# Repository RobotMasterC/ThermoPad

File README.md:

# ThermoPad

*Image drawn by Ever*

*https://www.youtube.com/@Ever_Draws*

A Thermometer that uses a SHT30-DIS-B2.5KS, a 0.96" OLED screen, and is controlled with a Xiao RP2040

## PCB

   - Front

   - Back

   - Schematic

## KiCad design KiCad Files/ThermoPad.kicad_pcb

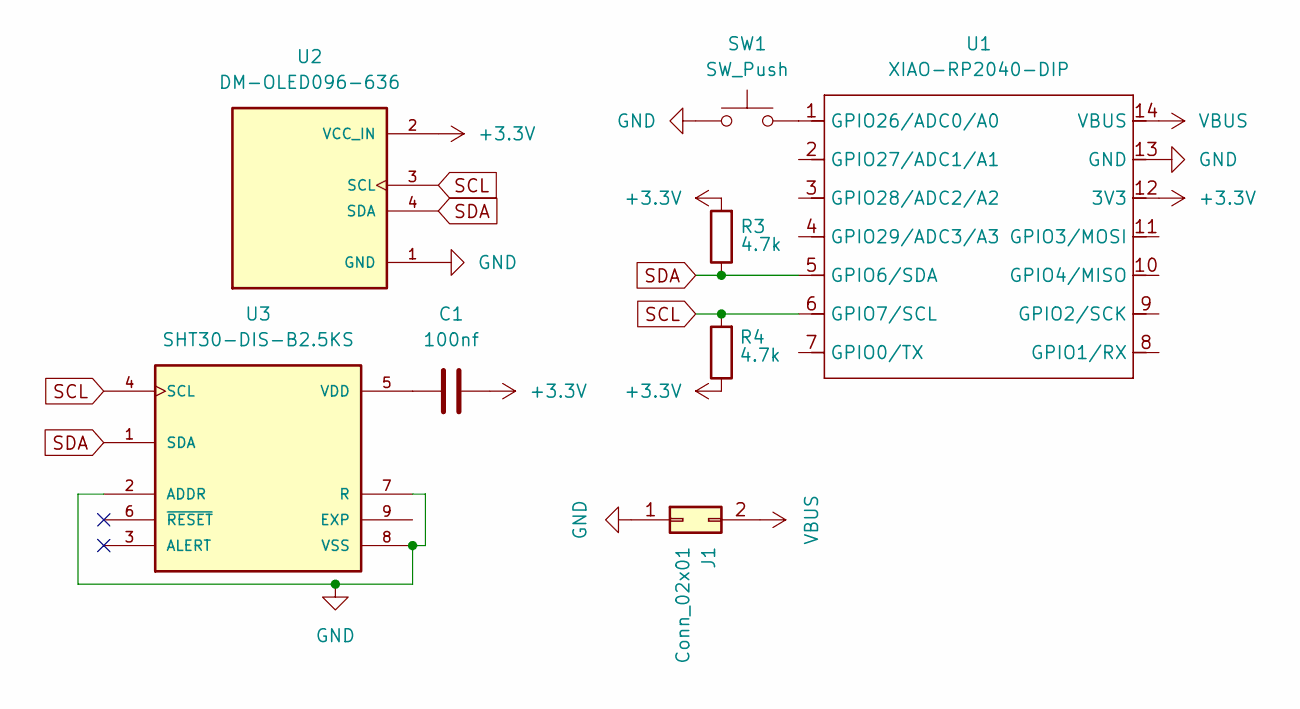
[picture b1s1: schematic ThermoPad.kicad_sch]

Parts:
C1: 100nf; C_0402_1005Metric
J1: Conn_02x01; PinHeader_1x02_P2.54mm_Horizontal
R3, R4: 4.7k; R_0402_1005Metric
SW1: SW_Push; SW_PUSH_6mm_H4.3mm
U1: XIAO-RP2040-DIP
U2: DM-OLED096-636; MODULE_DM-OLED096-636; PARTREV 2018-09-10
U3: SHT30-DIS-B2.5KS; XDCR_SHT30-DIS-B2.5KS

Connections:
+3.3V: C1.2, R3.2, R4.1, U1.12 (3V3), U2.2 (VCC_IN)
GND: J1.1, SW1.1, U1.13 (GND), U2.1 (GND), U3.2 (ADDR), U3.7 (R), U3.8 (VSS)
unnamed: SW1.2, U1.1 (GPIO26/ADC0/A0)
unnamed: C1.1, U3.5 (VDD)
SCL: R4.2, U1.6 (GPIO7/SCL), U2.3 (SCL), U3.4 (SCL)
SDA: R3.1, U1.5 (GPIO6/SDA), U2.4 (SDA), U3.1 (SDA)
VBUS: J1.2, U1.14 (VBUS)

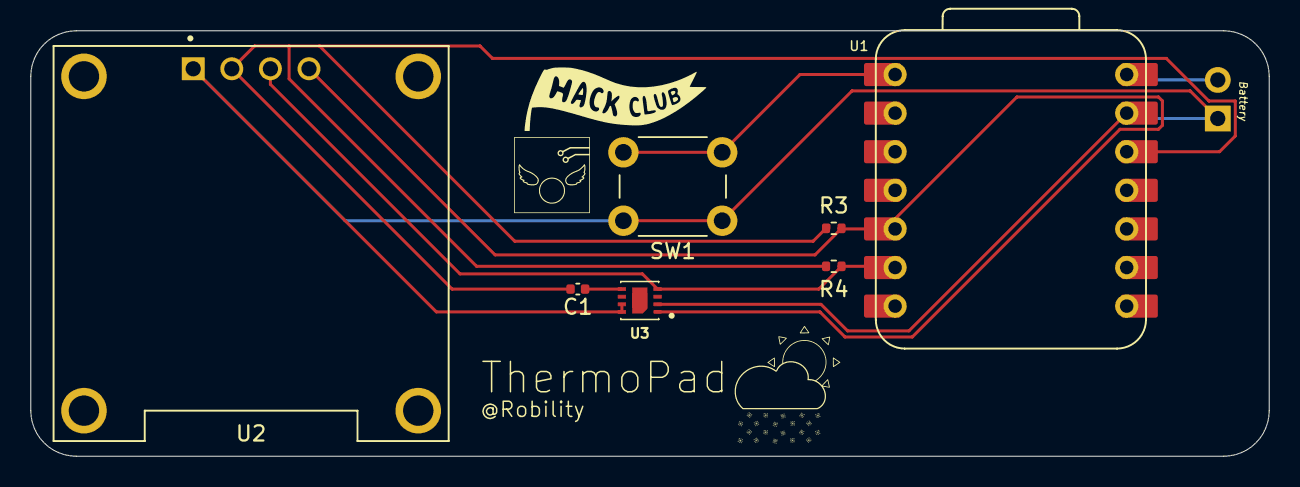
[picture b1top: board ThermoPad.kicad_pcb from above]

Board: 2 copper layers, 81.5 x 28.0 mm, 8 parts (1 on the bottom side), 7 nets.

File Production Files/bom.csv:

Designator,Footprint,Quantity,Value,LCSC Part #
C1,0402,1,100nf,
J1,PinHeader_1x02_P2.54mm_Horizontal,1,Conn_02x01,
"R3, R4",0402,2,4.7k,
SW1,SW_PUSH_6mm_H4.3mm,1,SW_Push,
U1,XIAO-RP2040-DIP,1,XIAO-RP2040-DIP,
U2,MODULE_DM-OLED096-636,1,DM-OLED096-636,
U3,XDCR_SHT30-DIS-B2.5KS,1,SHT30-DIS-B2.5KS,

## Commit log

2025-10-27 Update Pull-Up Resistors
